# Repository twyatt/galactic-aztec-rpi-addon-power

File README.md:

# About

Board designed to provide external power (e.g. using 2-3S LiPo batteries) for Raspberry Pis onboard the [Galactic Aztec] rocket.

Supports 6-14 VDC input and allows tuning of output voltage between 4.64 and 5.27 VDC to the Raspberry Pi 5V GPIO pins.
**NOTE: RTRIM1 is incorrectly labelled as 2k and a 2.5k resistor should be used instead to put the output voltage at the expected range.**

The design features the [LTC4412HV] to act as an [ideal safety diode], which is advised for Raspberry Pi HATs.

*The hope was to utilize the power switch-over features of the [LTC4412HV], allowing for the Raspberry Pi to be powered via USB and upon disconnecting, automatically switch over to the auxiliary power input, but in testing this feature did not function properly. Power was drawn from both sources when connected rather than completely switching between the available power sources.*

Custom EagleCAD parts on this board can be found in the [SDSU Rocket Eagle Libraries].

# Bill of Materials

| Qty | Name      | Description                                  | Part Number       | Vendor   |
|:---:|-----------|----------------------------------------------|------------------:|----------|
| 1   | CI2       | Capacitor 47µF 35V 63mA SMD                  | [493-2202-1-ND]   | DigiKey  |
| 1   | CI1       | Capacitor 22µF 35V 45mA SMD                  | [493-9805-1-ND]   | DigiKey  |
| 1   | R1        | Resistor 100kΩ 1/4W 1% 0603                  | [RHM100KADCT-ND]  | DigiKey  |
| 1   | IC1       | DC to DC Converter 6A                        | [555-1125-1-ND]   | DigiKey  |
| 1   | RTRIM1    | Resistor 2kΩ 0603                            | [P2.00KHCT-ND]    | DigiKey  |
| 1   | RTRIM2    | Resistor 2.49kΩ 0603                         | [RHM2.49KCFCT-ND] | DigiKey  |
| 1   | RTRIM3    | Potentiometer 1kΩ 10% 3/4W 20                | [987-1160-ND]     | DigiKey  |
| 1   | RTRIM_ALT | Resistor 1.33kΩ 0.1% 1/10W 0603              | [P1.33KDBCT-ND]   | DigiKey  |
| 1   | RTUNE     | Resistor 220Ω 1% 1/10W 0603                  | [RHM220CFCT-ND]   | DigiKey  |
| 1   | CTUNE     | Capacitor 3900pF 25V 5%                      | [445-2665-1-ND]   | DigiKey  |
| 2   | CO1, CO2  | Capacitor 47µF 35V 63mA SMD                  | [493-2202-1-ND]   | DigiKey  |
| 3   | C[2-4]    | Capacitor 10µF 16V 0603                      | [490-7198-1-ND]   | DigiKey  |
| 1   | R3        | Resistor 470kΩ 1% 1/4W 0603                  | [P470KBYCT-ND]    | DigiKey  |
| 1   | IC2       | LTC4412HV Source Selector Switch IC SOT-23-6 | [LTC4412HVIS6]    | DigiKey  |
| 1   |           | MOSFET P-Channel 1.8V Vdss=12V Id=6A SOT23-6 | [FDC606PCT-ND]    | DigiKey  |
| 1   |           | Capacitor 1000µF 20% 10V 310mA SMD           | [493-2171-1-ND]   | DigiKey  |
| 1   |           | Capacitor 820µF 20% 16V 80mΩ 510mA SMD       | [1189-2069-1-ND]  | DigiKey  |
| 1   |           | Capacitor 10uF 20% 16V 0603                  | [490-7198-1-ND]   | DigiKey  |
| 1   |           | Molex Mini Fit Jr. 4-pos Right Angle         | [WM1352-ND]       | DigiKey  |
| 1   | D4        | LED Red Vf=1.8V If=2mA 0603                  | [475-1195-2-ND]   | DigiKey  |
| 1   | R4        | Resistor 1.8kΩ 1/4W 1% 0603                  | [P1.8KBYCT-ND]    | DigiKey  |
| 1   |           | Header Stacking 2x20 Tall 23mm               | [1979]            | Adafruit |

[Galactic Aztec]: http://rocket.sdsu.edu/rockets
[LTC4412HV]: http://www.linear.com/product/LTC4412HV
[ideal safety diode]: https://github.com/raspberrypi/hats/blob/master/designguide.md#back-powering-the-pi-via-the-j8-gpio-header
[SDSU Rocket Eagle Libraries]: https://github.com/twyatt/SDSURocket-Eagle-Libraries
[493-2202-1-ND]: http://www.digikey.com/product-detail/en/UWT1V470MCL1GS/493-2202-1-ND/590177
[493-9805-1-ND]: http://www.digikey.com/product-detail/en/UWJ1V220MCL1GB/493-9805-1-ND/3963137
[RHM100KADCT-ND]: http://www.digikey.com/product-detail/en/ESR03EZPF1003/RHM100KADCT-ND/1983754
[555-1125-1-ND]: http://www.digikey.com/product-detail/en/APTS006A0X-SRZ/555-1125-1-ND/1766113
[P2.00KHCT-ND]: http://www.digikey.com/product-detail/en/ERJ-3EKF2001V/P2.00KHCT-ND/198219
[RHM2.49KCFCT-ND]: http://www.digikey.com/product-detail/en/MCR03ERTF2491/RHM2.49KCFCT-ND/2796475
[987-1160-ND]: http://www.digikey.com/product-detail/en/89PR1KLF/987-1160-ND/2408738
[P1.33KDBCT-ND]: http://www.digikey.com/product-detail/en/ERA-3AEB1331V/P1.33KDBCT-ND/3075785
[RHM220CFCT-ND]: http://www.digikey.com/product-detail/en/MCR03ERTF2200/RHM220CFCT-ND/2796470
[445-2665-1-ND]: http://www.digikey.com/product-detail/en/C1608C0G1E392J080AA/445-2665-1-ND/970490
[493-2202-1-ND]: http://www.digikey.com/product-detail/en/UWT1V470MCL1GS/493-2202-1-ND/590177
[490-7198-1-ND]: http://www.digikey.com/product-detail/en/GRM188C81C106MA73D/490-7198-1-ND/3900421
[P470KBYCT-ND]: http://www.digikey.com/product-detail/en/ERJ-PA3F4703V/P470KBYCT-ND/5036197
[LTC4412HVIS6]: http://www.digikey.com/product-detail/en/LTC4412HVIS6%23TRMPBF/LTC4412HVIS6%23TRMPBFCT-ND/3232334
[FDC606PCT-ND]: http://www.digikey.com/product-detail/en/FDC606P/FDC606PCT-ND/1626185
[493-2171-1-ND]: http://www.digikey.com/product-detail/en/UWT1A102MNL1GS/493-2171-1-ND/590146
[1189-2069-1-ND]: http://www.digikey.com/product-detail/en/16TKV820M10X10.5/1189-2069-1-ND/3986988
[490-7198-1-ND]: http://www.digikey.com/product-detail/en/GRM188C81C106MA73D/490-7198-1-ND/3900421
[WM1352-ND]: http://www.digikey.com/product-search/en?x=0&y=0&lang=en&site=us&keywords=538-39-30-1040
[475-1195-2-ND]: http://www.digikey.com/product-detail/en/LS%20L29K-H1J2-1-Z/475-1195-1-ND/810356
[P1.8KBYCT-ND]: http://www.digikey.com/product-detail/en/ERJ-PA3F1801V/P1.8KBYCT-ND/5036145
[1979]: http://www.adafruit.com/products/1979

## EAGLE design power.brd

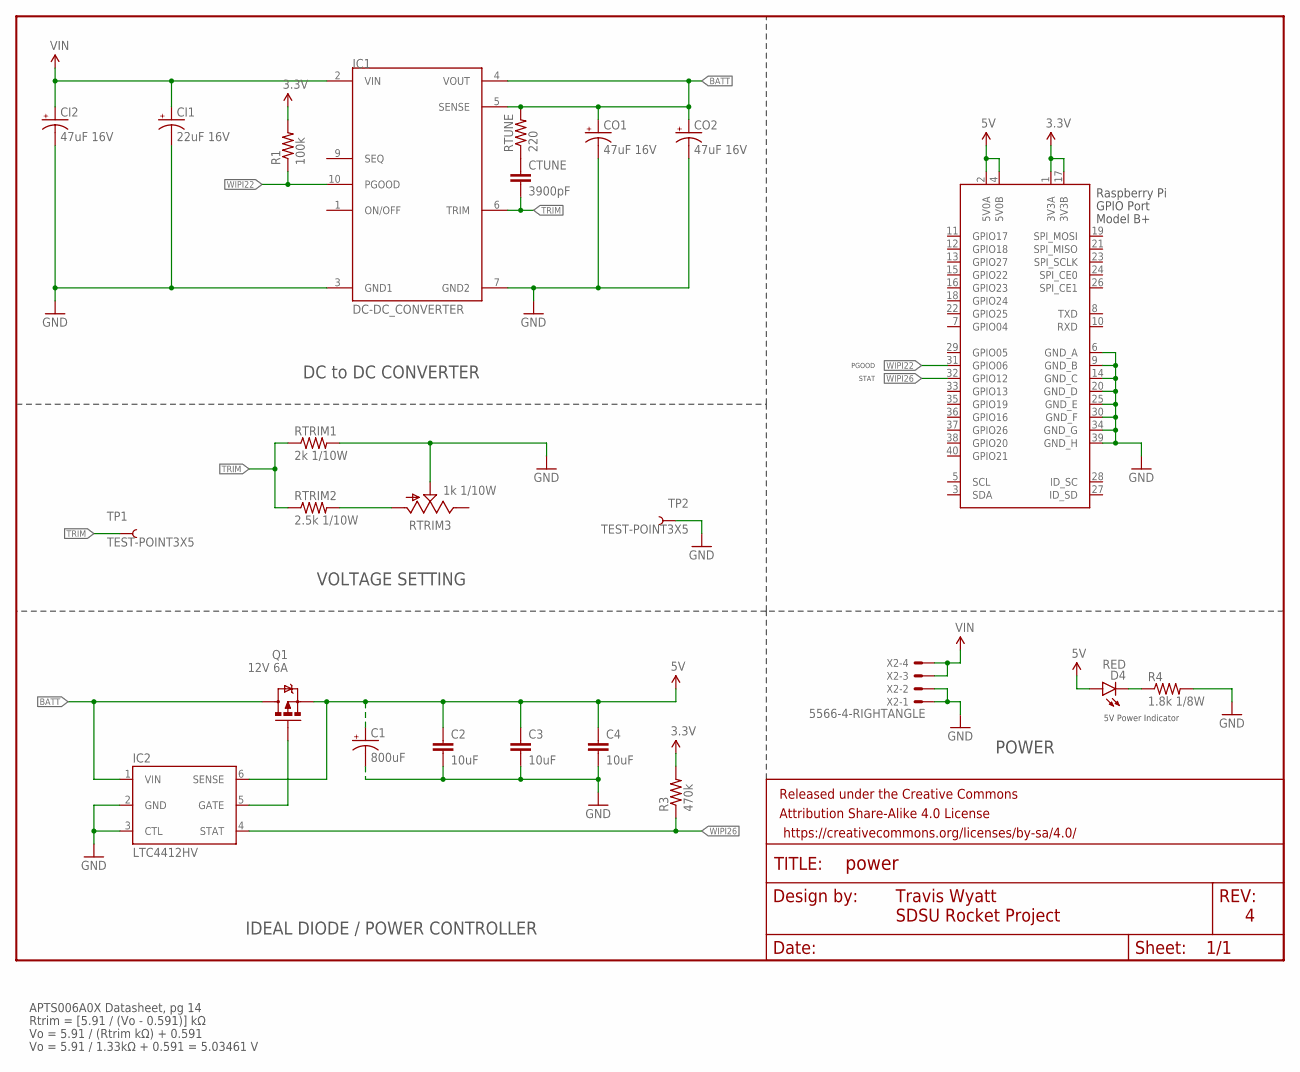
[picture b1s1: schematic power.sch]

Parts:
C1: 800uF; PANASONIC_G
C2, C3, C4: 10uF; 0603-CAP
CI1: 22uF 16V; NIPPON_F80
CI2: 47uF 16V; NIPPON_F80
CO1, CO2: 47uF 16V; NIPPON_F80
CTUNE: 3900pF; 0603-CAP
D4: RED; LED-0603
FRAME1: FRAME-LETTER; CREATIVE_COMMONS
IC1: DC-DC_CONVERTER
IC2: LTC4412HV; SOT23-6
Q1: 12V 6A; SSOT-6L
R1: 100k; 0603-RES
R3: 470k; 0603-RES
R4: 1.8k 1/8W; 0603-RES
RTRIM1: 2k 1/10W; 0603-RES
RTRIM2: 2.5k 1/10W; 0603-RES
RTRIM3: 1k 1/10W; 89P
RTUNE: 220; 0603-RES
TP1, TP2: TEST-POINT3X5; PAD.03X.05
X2: 5566-4-RIGHTANGLE; 5566-4
X3: RASPI_BOARD_B+#_H; RASPI_BOARD_B+HAT

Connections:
3.3V: R1.2, R3.2, X3.1 (3V3A), X3.17 (3V3B)
5V: C1.+, C2.1, C3.1, C4.1, D4.A, IC2.6 (SENSE), Q1.4 (S), X3.2 (5V0A), X3.4 (5V0B)
BATT: CO1.+, CO2.+, IC1.4 (VOUT), IC1.5 (SENSE), IC2.1 (VIN), Q1.1 (D), Q1.2 (D), Q1.5 (D), Q1.6 (D), RTUNE.2
GND: C1.-, C2.2, C3.2, C4.2, CI1.-, CI2.-, CO1.-, CO2.-, IC1.3 (GND1), IC1.7 (GND2), IC2.2 (GND), IC2.3 (CTL), R4.2, RTRIM1.2, RTRIM3.2 (S), TP2.P$1, X2.1, X2.2, X3.6 (GND_A), X3.9 (GND_B), X3.14 (GND_C), X3.20 (GND_D), X3.25 (GND_E), X3.30 (GND_F), X3.34 (GND_G), X3.39 (GND_H)
unnamed: IC2.5 (GATE), Q1.3 (G)
unnamed: CTUNE.1, RTUNE.1
unnamed: RTRIM2.2, RTRIM3.1 (A)
unnamed: D4.C, R4.1
TRIM: CTUNE.2, IC1.6 (TRIM), RTRIM1.1, RTRIM2.1, TP1.P$1
VIN: CI1.+, CI2.+, IC1.2 (VIN), X2.3, X2.4
WIPI22: IC1.10 (PGOOD), R1.1, X3.31 (GPIO06)
WIPI26: IC2.4 (STAT), R3.1, X3.32 (GPIO12)

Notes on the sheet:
Rtrim = [5.91 / (Vo - 0.591)] kΩ
Vo = 5.91 / (Rtrim kΩ) + 0.591
Vo = 5.91 / 1.33kΩ + 0.591 = 5.03461 V
APTS006A0X Datasheet, pg 14
5V Power Indicator
POWER
Travis Wyatt
SDSU Rocket Project
DC to DC CONVERTER
VOLTAGE SETTING
IDEAL DIODE / POWER CONTROLLER
STAT
PGOOD

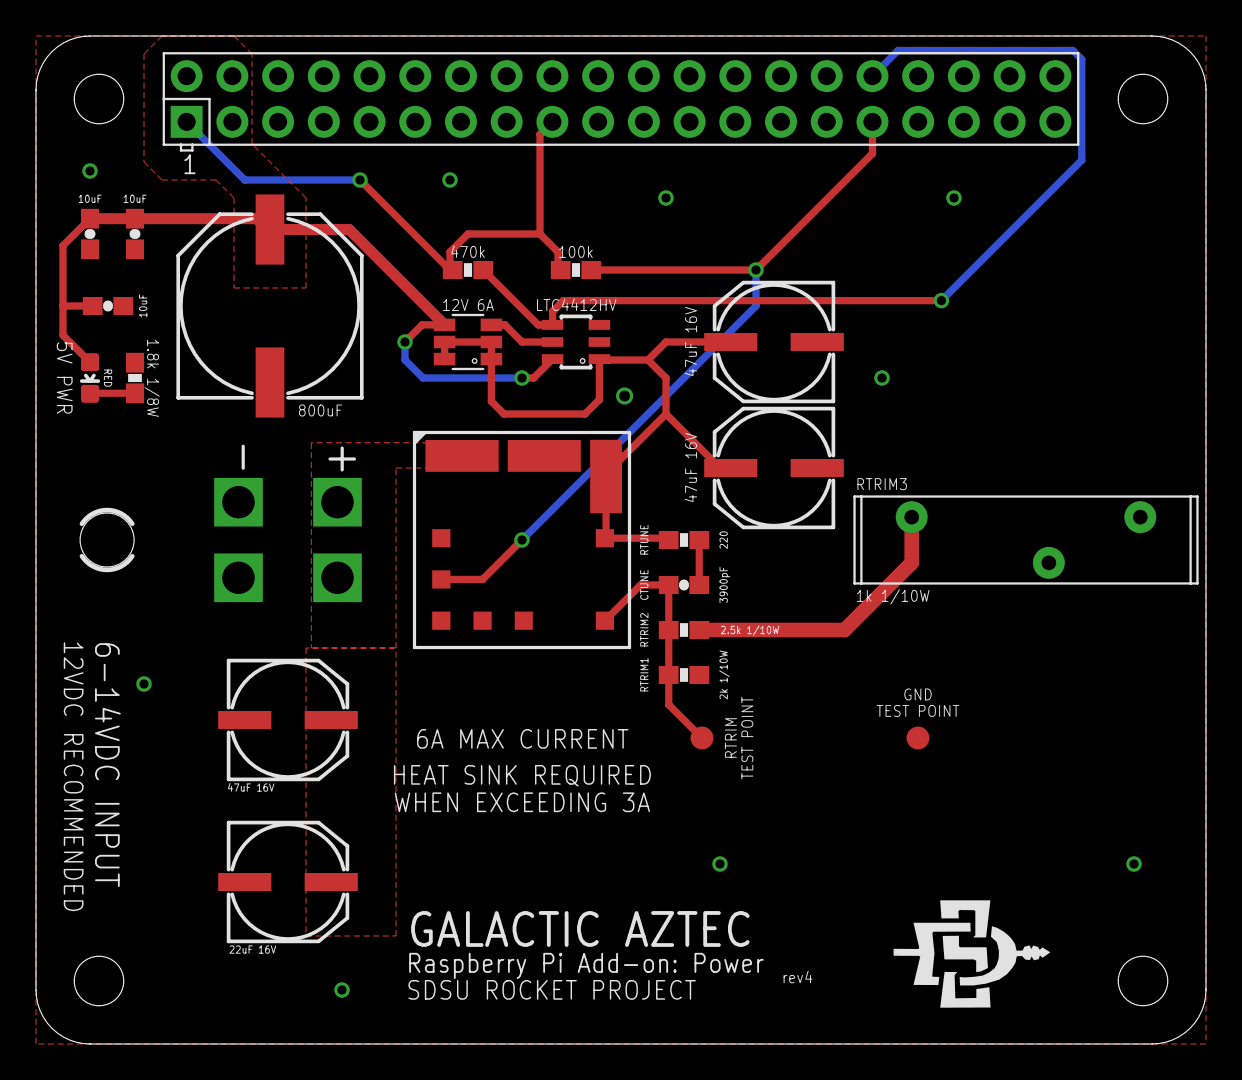
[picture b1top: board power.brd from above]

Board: 2 copper layers, 65.0 x 56.0 mm, 25 parts (0 on the bottom side), 12 nets.

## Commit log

2015-08-22 Fix molex connector thru hole size
2015-08-25 Add DC to DC converter and ideal safety diode
2015-08-25 Optimize design and add voltage tuning
    Updated design for more capacitor reuse and added additional capacitors
    to help stabilize power. Added variable resistor to allow for fine
    tuning voltage output. Improved labeling of components on the schematic.
2015-08-25 Fix variable resistor thru holes
    The thru hole positions and size for the variable resistor (RTRIM3) were
    fixed to have the component sit on the top side of the board.

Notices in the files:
parts and their libraries:
SparkFun-Resistors: Licensing: Creative Commons ShareAlike 4.0 International - https://creativecommons.org/licenses/by-sa/4.0
SparkFun-Aesthetics: Released under the Creative Commons Attribution Share-Alike 4.0 License
SparkFun-Aesthetics: https://creativecommons.org/licenses/by-sa/4.0
